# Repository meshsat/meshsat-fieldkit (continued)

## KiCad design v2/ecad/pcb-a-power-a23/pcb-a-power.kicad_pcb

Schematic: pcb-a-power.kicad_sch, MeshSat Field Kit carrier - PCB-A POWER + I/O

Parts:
C1, C2: 47u 25V; C_1206_3216Metric
C3, C29, C30, C35, C36, C41, C42, C47, C48, C54, C120: 10u 25V 1210; C_1210_3225Metric
C4, C19: 1u; C_0603_1608Metric
C5, C26, C53, C57, C68, C75, C86, C98, C100, C102: 10n; C_0603_1608Metric
C6, C58, C69, C76, C87: 100p; C_0603_1608Metric
C7, C59, C70, C77, C88: 47n; C_0603_1608Metric
C8, C60, C71, C78, C89: 4.7u; C_0805_2012Metric
C9, C10, C16, C17, C61, C62, C72, C73, C79, C80, C90, C91: 100n 25V; C_0603_1608Metric
C11, C12, C13, C14, C15, C63, C64, C65, C66, C67, C74, C81, C82, C92, C108, C109, C110, C111, C116, C117, C118, C119: 10u 50V X7R 1210; C_1210_3225Metric
C18: 3.3u; C_0805_2012Metric
C20, C21, C22: 10u 35V 1210; C_1210_3225Metric
C23, C24, C25: 22u 25V 1210; C_1210_3225Metric
C27: 1n; C_0603_1608Metric
C28, C34, C40, C46, C52, C93, C95, C99, C101, C103, C104, C106, C107: 100n; C_0603_1608Metric
C31, C32, C33, C37, C38, C39, C43, C44, C45, C49, C50, C51, C55, C56: 22u 10V X7R 1210; C_1210_3225Metric
C83, C84, C85: 10u 100V X7R 1210; C_1210_3225Metric
C94: 220n; C_0603_1608Metric
C96, C97: 330p; C_0603_1608Metric
C112, C113, C114, C115: 3.3n; C_0603_1608Metric
D1: SMCJ18A (VBAT clamp); D_SMC; LCSC C374030
D2: SMCJ33A (VIN_RAW clamp behind E6's filter); D_SMC
D3: SMBJ5.0A; D_SMB
D4: SMBJ18A (VBUS clamp at the outlet); D_SMB
F1: 25 A mini blade (Keystone 3568 holder): pack node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; Fuseholder_Blade_Mini_Keystone_3568
J_5V_DEV: USB device rail to B16 (JST-VH): + -; JST_VH_B2P-VH_1x02_P3.96mm_Vertical; LCSC C274411
J_5V_S1: slot 1 5.1 V rail to B16 (JST-VH, 16 AWG): + -; JST_VH_B2P-VH_1x02_P3.96mm_Vertical; LCSC C274411
J_5V_S2: slot 2 5.1 V rail to B16 (JST-VH, 16 AWG): + -; JST_VH_B2P-VH_1x02_P3.96mm_Vertical; LCSC C274411
J_5V_S3: slot 3 5.1 V rail to B16 (JST-VH, 16 AWG): + -; JST_VH_B2P-VH_1x02_P3.96mm_Vertical; LCSC C274411
J_54V: 54 V to the PoE injector on B16 (JST-VH): + -; JST_VH_B2P-VH_1x02_P3.96mm_Vertical; LCSC C274411
J_AB1: A-B interconnect (IDC 2x13, top side) to B16's un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; IDC-Header_2x13_P2.54mm_Vertical_NarrowPad
J_AB2: A-B wall-port ribbon (IDC 2x5): the wall USB pair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; IDC-Header_2x05_P2.54mm_Vertical_NarrowPad
J_BM1, J_BM2, J_BM3, J_BM4, J_BM5, J_BM6, J_BM7, J_BM8, J_BM9, J_BM10, J_BM11: SMP-MAX slide-on receptacle R222M00720 (underside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; Radiall_SMPMAX_R222M00720
J_CN1, J_CN2, J_CN3, J_CN4: 9 A spring pin, pack return (Mill-Max 0858 class,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; Mill-Max_0858_power_pin
J_CP1, J_CP2, J_CP3, J_CP4: 9 A spring pin, CELL+ (Mill-Max 0858 class, dock 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; Mill-Max_0858_power_pin
J_DOCK: spring pins to the dock block (2x6, Preci-Dip 813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; PogoPins_2x6
J_HEAT: JST-XH 1x2 socket: the heater mat under the 2590 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; JST_XH_B2B-XH-A_1x02_P2.50mm_Vertical; LCSC C265283
J_HF: 12.0 V to the QMX HF unit in its lid tray (JST-VH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; JST_VH_B2P-VH_1x02_P3.96mm_Vertical; LCSC C274411
J_MAINSW: JST-XH 1x2 socket: the MAIN button lead from the 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; JST_XH_B2B-XH-A_1x02_P2.50mm_Vertical; LCSC C265283
J_MEZZ1: D8 mezzanine harness (IDC 2x8): its USB pair, the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; IDC-Header_2x08_P2.54mm_Vertical_NarrowPad
J_MEZZ_PWR1: D8 mezzanine 5 V (JST-VH): + -; JST_VH_B2P-VH_1x02_P3.96mm_Vertical; LCSC C274411
J_MON: monitor supply lead to the Xenarc (JST-VH): + -; JST_VH_B2P-VH_1x02_P3.96mm_Vertical; LCSC C274411
J_PA: 13.8 V to the PA module on the face plate (JST-VH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; JST_VH_B2P-VH_1x02_P3.96mm_Vertical; LCSC C274411
J_PRE1: pre-charge pin, longer, mates first (32.24 AX); Mill-Max_0858_power_pin
J_RF1, J_RF2, J_RF3, J_RF4, J_RF5, J_RF6, J_RF7, J_RF8, J_RF9, J_RF10, J_RF11: SMA jack, Amphenol 132134-11 vertical (pigtail to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; SMA_Amphenol_132134-11_Vertical; LCSC C3174425
J_USBC_OUT: wall USB-C outlet, power side (pigtail header): V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; PinHeader_1x05_P2.54mm_Vertical
J_USBW: JST-PH 1x4 socket: the wall USB-C data pair to B1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; JST_PH_B4B-PH-K_1x04_P2.00mm_Vertical; LCSC C131334
L1: 10uH XAL1010-103ME (Isat 14 A); L_Coilcraft_XAL1010-XXX
L2: 3.3uH XAL6030-332ME (Isat 12.2 A); L_Coilcraft_XAL6060-XXX
L3, L4, L5, L6: 4.7uH XAL6060-472ME (Isat 11 A); L_Coilcraft_XAL6060-XXX
L7: 4.7uH XAL4030-472ME; L_Coilcraft_XAL4030-XXX
L8: 6.8uH XAL1010-682ME (Isat 17 A); L_Coilcraft_XAL1010-XXX
L9, L11: 6.8uH XAL1010-682ME; L_Coilcraft_XAL1010-XXX
L10: 22uH XAL1010-223ME (Isat 9 A); L_Coilcraft_XAL1010-XXX
Q1: 2N7002: panel controller high = pull KILL low = p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; SOT-23
Q2, Q3, Q4, Q5, Q17, Q18, Q19, Q20: CSD19532Q5B 100 V N-FET (4.6 mOhm at VGS 6 V, Pow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; PowerPAK_SO-8_Single; LCSC C473333
Q6: 2N7002: CHG_INHIBIT high = ILIM_HIZ low = charger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; SOT-23
Q7, Q8, Q9, Q10, Q11, Q12, Q13, Q14, Q15, Q16, Q21, Q22, Q23, Q24, Q25, Q26: CSD18510Q5B 40 V N-FET; PowerPAK_SO-8_Single
Q27: CSD18510Q5B 40 V N-FET (VBUS switch); PowerPAK_SO-8_Single
R1: 10R 2W 2512; R_2512_6332Metric
R2, R3, R4, R5, R13, R21, R30, R34, R38, R42, R57, R73, R102, R103, R104, R111, R112, R113, R114, R116, R118, R123, R128, R143, R145: 100k; R_0603_1608Metric
R6: 240k 1%; R_0603_1608Metric
R7, R15, R29, R33, R37, R41, R49, R51, R59, R61, R67, R75, R125, R134: 10k 1%; R_0603_1608Metric
R8, R52, R62, R68, R78: 40.2k (300 kHz); R_0603_1608Metric
R9, R53, R63, R69, R79: 30k (slope); R_0603_1608Metric
R10, R22, R23, R25, R44, R54, R64, R70, R80, R91, R95, R99, R110, R117, R142: 10k; R_0603_1608Metric
R11, R65, R81, R138: 10mOhm 1% 2512 (ISNS); R_2512_6332Metric
R12, R56, R122, R127: 5mOhm 1% 2512 (CS); R_2512_6332Metric
R14, R58, R74, R124, R133: 62k 1%; R_0603_1608Metric
R16: 10mOhm 1% 2512 (RAC, input current sense); R_2512_6332Metric
R17: 5mOhm 1% 2512 (RSR, charge current sense); R_2512_6332Metric
R18: 10R; R_0603_1608Metric
R19: 16.5k 1%; R_0603_1608Metric
R20: 34.8k 1%; R_0603_1608Metric
R24: 10k (PSYS load); R_0603_1608Metric
R26: 60.4k 1% (CELL_BATPRESZ: 4S per Table, from VDDA); R_0603_1608Metric
R27: 40.2k 1%; R_0603_1608Metric
R28, R32, R36, R40: 53.6k 1%; R_0603_1608Metric
R31, R35, R39, R43: 5mOhm 1% 2512 (shunt); R_2512_6332Metric
R45, R46, R47, R115: 68k (RT: 500 kHz); R_0603_1608Metric
R48: 31.6k 1%; R_0603_1608Metric
R50: 162k 1%; R_0603_1608Metric
R55: 2mOhm 1% 2512 (ISNS); R_2512_6332Metric
R60: 140k 1%; R_0603_1608Metric
R66: 665k 1%; R_0603_1608Metric
R71: 20mOhm 1% 2512 (ISNS); R_2512_6332Metric
R72: 10mOhm 1% 2512 (CS); R_2512_6332Metric
R76: 105k 1%; R_0603_1608Metric
R77: 20k 1% (R_FBL); R_0603_1608Metric
R90: 750R 1% (ILM: 1.2 A); R_0603_1608Metric
R92, R96, R100: 100k 1%; R_0603_1608Metric
R93, R97, R101: 10k 1% (OVLO); R_0603_1608Metric
R94: 909R 1% (ILM: 1.0 A); R_0603_1608Metric
R98: 453R 1% (ILM: 2.0 A); R_0603_1608Metric
R119, R120, R121, R126, R135: 100k (MODE: CCM); R_0603_1608Metric
R129, R130, R131, R132: 22k; R_0603_1608Metric
R136: 21.0k 1% (R_FBL2: 9 V when CTL2 is low); R_0603_1608Metric
R137: 14.0k 1% (R_FBL1: 15 V when CTL1 is low too); R_0603_1608Metric
R139: 43R 1W 2512 (DSCG); R_2512_6332Metric
R140: 1M (GD to VPWR, 9.1.3); R_0603_1608Metric
R141: 698k; R_0603_1608Metric
TP3: EXP2_SP3; TestPoint_Pad_D1.5mm
TP4: EXP2_SP4; TestPoint_Pad_D1.5mm
TP5: EXP2_SP5; TestPoint_Pad_D1.5mm
TP6: EXP2_SP6; TestPoint_Pad_D1.5mm
TP7: EXP2_SP7; TestPoint_Pad_D1.5mm
TP8: EXP2_SP8; TestPoint_Pad_D1.5mm
TP9: VBAT; TestPoint_Pad_D1.5mm
TP10: GND; TestPoint_Pad_D1.5mm
TP11: +3V3; TestPoint_Pad_D1.5mm
TP12: VBUS20; TestPoint_Pad_D1.5mm
TP13: VIN_RAW; TestPoint_Pad_D1.5mm
TP14: CELL+; TestPoint_Pad_D1.5mm
TP15: EMCON_HW; TestPoint_Pad_D1.5mm
TP16: RAIL_EN; TestPoint_Pad_D1.5mm
TP17: SDA; TestPoint_Pad_D1.5mm
TP18: SCL; TestPoint_Pad_D1.5mm
TP19: IADPT; TestPoint_Pad_D1.5mm
TP20: IBAT; TestPoint_Pad_D1.5mm
TP21: DOCK_SPARE; TestPoint_Pad_D1.5mm
TP22: REGN; TestPoint_Pad_D1.5mm
TP23: EXP2_SPA; TestPoint_Pad_D1.5mm
TP24: EXP2_SPB; TestPoint_Pad_D1.5mm
TP25: EXP2_SPC; TestPoint_Pad_D1.5mm
TP26: EXP2_SPD; TestPoint_Pad_D1.5mm
TP27: AB_SPARE; TestPoint_Pad_D1.5mm
U1: LTC2954CTS8-1 push-button on/off controller; TSOT-23-8; LCSC C683782
U2: LM5176PWPR buck-boost controller, VBUS20 from VIN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; HTSSOP-28-1EP_4.4x9.7mm_P0.65mm_EP2.85x5.4mm; LCSC C442493
U3: BQ25731RSNR 1 to 5 cell buck-boost charger, 4S fr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; QFN-32-1EP_4x4mm_P0.4mm_EP2.65x2.65mm; LCSC C2871872
U4: AP64500SP-13 5 A buck, 5.1 V rail +5V_S1; SOIC-8-1EP_3.9x4.9mm_P1.27mm_EP2.29x3mm; LCSC C2070920
U5: AP64500SP-13 5 A buck, 5.1 V rail +5V_S2; SOIC-8-1EP_3.9x4.9mm_P1.27mm_EP2.29x3mm; LCSC C2070920
U6: AP64500SP-13 5 A buck, 5.1 V rail +5V_S3; SOIC-8-1EP_3.9x4.9mm_P1.27mm_EP2.29x3mm; LCSC C2070920
U7: AP64500SP-13 5 A buck, 5.1 V rail +5V_DEV; SOIC-8-1EP_3.9x4.9mm_P1.27mm_EP2.29x3mm; LCSC C2070920
U8: INA226 rail monitor +5V_S1; VSSOP-10_3x3mm_P0.5mm; LCSC C49851
U9: INA226 rail monitor +5V_S2; VSSOP-10_3x3mm_P0.5mm; LCSC C49851
U10: INA226 rail monitor +5V_S3; VSSOP-10_3x3mm_P0.5mm; LCSC C49851
U11: INA226 rail monitor +5V_DEV; VSSOP-10_3x3mm_P0.5mm; LCSC C49851
U12: TPS62933DRLR 3 A buck, 3.3 V logic; SOT-583-8; LCSC C3200405
U13: LM5176PWPR buck-boost controller, +13V8_PA from V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; HTSSOP-28-1EP_4.4x9.7mm_P0.65mm_EP2.85x5.4mm; LCSC C442493
U14: INA226 PA rail monitor (0x46); VSSOP-10_3x3mm_P0.5mm; LCSC C49851
U15: LM5176PWPR buck-boost controller, +12V_HF from VB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; HTSSOP-28-1EP_4.4x9.7mm_P0.65mm_EP2.85x5.4mm; LCSC C442493
U16: LM5176PWPR buck-boost controller, +54V_POE from V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; HTSSOP-28-1EP_4.4x9.7mm_P0.65mm_EP2.85x5.4mm; LCSC C442493
U17: INA226 PoE rail monitor (0x47); VSSOP-10_3x3mm_P0.5mm; LCSC C49851
U18: TPS25740ARGER USB-C PD source controller, 45 W ou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; QFN-24-1EP_4x4mm_P0.5mm_EP2.5x2.5mm; LCSC C544309
U19: LM5176PWPR buck-boost controller, PD_VPWR from VB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; HTSSOP-28-1EP_4.4x9.7mm_P0.65mm_EP2.85x5.4mm; LCSC C442493
U21: TPS259631DDAR eFuse VBAT -> VMON (750R 1% (ILM: 1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; SOIC-8-1EP_3.9x4.9mm_P1.27mm_EP2.29x3mm; LCSC C2155778
U22: TPS259631DDAR eFuse VBAT -> VHEAT (909R 1% (ILM: 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; SOIC-8-1EP_3.9x4.9mm_P1.27mm_EP2.29x3mm; LCSC C2155778
U23: TPS259631DDAR eFuse +5V_DEV -> +5V_D8 (453R 1% (I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; SOIC-8-1EP_3.9x4.9mm_P1.27mm_EP2.29x3mm; LCSC C2155778
U26: SN74LVC08APWR quad AND: EMCON gates for the PA ra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; TSSOP-14_4.4x5mm_P0.65mm; LCSC C465737
U27: PCA9555PW (0x21): enables and status; TSSOP-24_4.4x7.8mm_P0.65mm; LCSC C2864778
U28: PCA9555PW (0x24): power-good lines, spares; TSSOP-24_4.4x7.8mm_P0.65mm; LCSC C2864778
U29: USBLC6-2SC6; SOT-23-6; LCSC C7519

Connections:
+3V3: C55.1, C56.1, C104.1, C106.1, C107.1, D3.1 (A1), J_MEZZ1.13, L7.2, R3.2, R13.2, R22.2, R23.2, R44.2, R48.1, R57.2, R73.2, R91.2, R95.2, R99.2, R110.2, R117.2, R123.2, R128.2, R142.2, TP11.1, U8.6, U9.2, U9.6, U10.1, U10.6, U11.1, U11.2, U11.6, U14.1, U14.6, U17.1, U17.6, U26.14, U27.21 (A0), U27.24 (VDD), U28.3 (A2), U28.24 (VDD)
/+5V_D8: J_MEZZ_PWR1.1, U23.5
/+5V_DEV: C49.1, C50.1, C51.1, C103.1, J_5V_DEV.1, R40.1, R43.2, R100.1, U11.8, U11.9, U18.17, U23.4, U29.5 (VBUS)
/+5V_S1: C31.1, C32.1, C33.1, J_5V_S1.1, R28.1, R31.2, U8.8, U8.9
/+5V_S2: C37.1, C38.1, C39.1, J_5V_S2.1, R32.1, R35.2, U9.8, U9.9
/+5V_S3: C43.1, C44.1, C45.1, J_5V_S3.1, R36.1, R39.2, U10.8, U10.9
/+12V_HF: C109.1, C110.1, C111.1, J_HF.1, R60.1, R65.2, U15.12, U15.13, U15.24
/+13V8_PA: C65.1, C66.1, C67.1, J_PA.1, R50.1, R55.2, U13.12, U13.13, U13.24, U14.8, U14.9
/+54V_POE: C83.1, C84.1, C85.1, J_54V.1, R66.1, R71.2, U16.12, U16.13, U17.9
/AB_SPARE: J_MEZZ1.16, TP27.1
/B33_BST: C52.1, U12.6
/B33_FB: R48.2, R49.1, U12.8
/B33_SS: C53.1, U12.7
/B33_SW: C52.2, L7.1, U12.5
/CELL+: F1.1, J_CP1.1, J_CP2.1, J_CP3.1, J_CP4.1, R1.2, R17.2, TP14.1, U3.19
/CHG_ILIM: Q6.3 (D), R19.2, R20.1, U3.6
/CHG_INHIBIT: Q6.1 (G), R21.1, U27.4 (IO0_0)
/CHRG_OK: R22.1, U3.4, U27.13 (IO1_0)
/CH_ACN: C20.1, C21.1, C22.1, Q7.5, R16.2, U3.2
/CH_BTST1: C16.1, U3.30
/CH_BTST2: C17.1, U3.25
/CH_CELL: R26.2, R27.1, U3.18
/CH_COMP1: R25.1, U3.16
/CH_COMP1C: C26.1, R25.2
/CH_COMP2: C27.1, U3.17
/CH_HIDRV1: Q7.4, U3.31
/CH_HIDRV2: Q10.4, U3.24
/CH_LODRV1: Q8.4, U3.29
/CH_LODRV2: Q9.4, U3.26
/CH_SRP: C23.1, C24.1, C25.1, Q10.5, R17.1, U3.20, U3.22
/CH_SW1: C16.2, L2.1, Q7.1, Q7.2, Q7.3, Q8.5, U3.32
/CH_SW2: C17.2, L2.2, Q9.5, Q10.1, Q10.2, Q10.3, U3.23
/CH_VDDA: C19.1, R18.2, R26.1, U3.7
/D8_EN: R113.1, U23.3, U27.7 (IO0_3)
/D8_FLT: R99.1, U23.6, U27.17 (IO1_4)
/DEV_EN: R42.1, U7.3, U27.11 (IO0_7)
/DOCK_SPARE: J_DOCK.12, TP21.1, U27.18 (IO1_5)
/EMCON_HW: J_AB1.15, R102.1, TP15.1, U26.1, U26.4
/EXP2_SP3: TP3.1, U28.15 (IO1_2)
/EXP2_SP4: TP4.1, U28.16 (IO1_3)
/EXP2_SP5: TP5.1, U28.17 (IO1_4)
/EXP2_SP6: TP6.1, U28.18 (IO1_5)
/EXP2_SP7: TP7.1, U28.19 (IO1_6)
/EXP2_SP8: TP8.1, U28.20 (IO1_7)
/EXP2_SPA: TP23.1, U28.4 (IO0_0)
/EXP2_SPB: TP24.1, U28.5 (IO0_1)
/EXP2_SPC: TP25.1, U28.6 (IO0_2)
/EXP2_SPD: TP26.1, U28.7 (IO0_3)
/EXP_INT: J_AB1.13, J_MEZZ1.12, R110.1, U27.1 (~INT), U28.1 (~INT)
/FE_BOOT1: C9.1, U2.26
/FE_BOOT2: C10.1, U2.20
/FE_COMP: C6.1, R10.1, U2.9
/FE_COMPC: C5.1, R10.2
/FE_CS: Q3.1, Q3.2, Q3.3, Q4.1, Q4.2, Q4.3, R12.1, U2.16
/FE_EN: R14.2, R15.1, U2.1
/FE_FB: R6.2, R7.1, U2.11
/FE_HDRV1: Q2.4, U2.27
/FE_HDRV2: Q5.4, U2.19
/FE_LDRV1: Q3.4, U2.25
/FE_LDRV2: Q4.4, U2.21
/FE_MODE: R119.1, U2.4
/FE_OUT: Q5.5, R11.1, U2.14
/FE_PGOOD: R13.1, U2.17, U27.20 (IO1_7)
/FE_RT: R8.1, U2.6
/FE_SLOPE: R9.1, U2.7
/FE_SS: C7.1, U2.8
/FE_SW1: C9.2, L1.1, Q2.1, Q2.2, Q2.3, Q3.5, U2.28
/FE_SW2: C10.2, L1.2, Q4.5, Q5.1, Q5.2, Q5.3, U2.18
/FE_VCC: C8.1, R119.2, U2.23
/HEAT_EN: R112.1, U22.3, U27.6 (IO0_2)
/HEAT_FLT: R95.1, U22.6, U27.16 (IO1_3)
/HF_BOOT1: C72.1, U15.26
/HF_BOOT2: C73.1, U15.20
/HF_COMP: C69.1, R64.1, U15.9
/HF_COMPC: C68.1, R64.2
/HF_CS: Q16.1, Q16.2, Q16.3, Q23.1, Q23.2, Q23.3, R122.1, U15.16
/HF_EN: R124.1, R124.2, R125.1, U15.1, U26.6
/HF_FB: R60.2, R61.1, U15.11
/HF_HDRV1: Q15.4, U15.27
/HF_HDRV2: Q24.4, U15.19
/HF_LDRV1: Q16.4, U15.25
/HF_LDRV2: Q23.4, U15.21
/HF_MODE: R126.1, U15.4
/HF_OUT: Q24.5, R65.1, U15.14
/HF_PGOOD: R123.1, U15.17, U28.10 (IO0_6)
/HF_RT: R62.1, U15.6
/HF_SLOPE: R63.1, U15.7
/HF_SS: C70.1, U15.8
/HF_SW1: C72.2, L9.1, Q15.1, Q15.2, Q15.3, Q16.5, U15.28
/HF_SW2: C73.2, L9.2, Q23.5, Q24.1, Q24.2, Q24.3, U15.18
/HF_SW_EN: R104.1, U26.5, U27.10 (IO0_6)
/HF_VCC: C71.1, R126.2, U15.23
/IADPT: TP19.1, U3.8
/IBAT: TP20.1, U3.9
/INA_ALERT: R44.1, U8.3, U9.3, U10.3, U11.3, U14.3, U17.3, U27.19 (IO1_6)
/KILL: Q1.3 (D), R4.1, U1.8
/MAIN_PB: J_MAINSW.1, U1.2
/MON_EN: R111.1, U21.3, U27.5 (IO0_1)
/MON_FLT: R91.1, U21.6, U27.15 (IO1_2)
/PA_BOOT1: C61.1, U13.26
/PA_BOOT2: C62.1, U13.20
/PA_COMP: C58.1, R54.1, U13.9
/PA_COMPC: C57.1, R54.2
/PA_CS: Q12.1, Q12.2, Q12.3, Q13.1, Q13.2, Q13.3, R56.1, U13.16
/PA_EN: J_MEZZ1.9, R58.1, R58.2, R59.1, U13.1, U26.3
/PA_FB: R50.2, R51.1, U13.11
/PA_HDRV1: Q11.4, U13.27
/PA_HDRV2: Q14.4, U13.19
/PA_LDRV1: Q12.4, U13.25
/PA_LDRV2: Q13.4, U13.21
/PA_MODE: R120.1, U13.4
/PA_OUT: Q14.5, R55.1, U13.14, U14.10
/PA_PGOOD: R57.1, U13.17, U28.8 (IO0_4)
/PA_RT: R52.1, U13.6
/PA_SLOPE: R53.1, U13.7
/PA_SS: C59.1, U13.8
/PA_SW1: C61.2, L8.1, Q11.1, Q11.2, Q11.3, Q12.5, U13.28
/PA_SW2: C62.2, L8.2, Q13.5, Q14.1, Q14.2, Q14.3, U13.18
/PA_SW_EN: R103.1, U26.2, U27.9 (IO0_5)
/PA_VCC: C60.1, R120.2, U13.23
/PD_BOOT1: C90.1, U19.26
/PD_BOOT2: C91.1, U19.20
/PD_CC1: C96.1, J_USBC_OUT.2, U18.2
/PD_CC2: C97.1, J_USBC_OUT.3, U18.3
/PD_COMP: C87.1, R80.1, U19.9
/PD_COMPC: C86.1, R80.2
/PD_CS: Q22.1, Q22.2, Q22.3, Q25.1, Q25.2, Q25.3, R127.1, U19.16
/PD_CTL1: R137.2, U18.6
/PD_CTL2: R136.2, U18.7
/PD_DSCG: R139.1, U18.24
/PD_DVDD: C94.1, U18.5, U18.8, U18.12, U18.13
/PD_EN: R133.1, R133.2, R134.1, R143.1, U19.1, U28.13 (IO1_0)
/PD_FB: R76.2, R77.1, R136.1, R137.1, U19.11
/PD_GD: R140.2, R141.1, U18.15
/PD_GDNG: Q27.4, U18.22
/PD_HDRV1: Q21.4, U19.27
/PD_HDRV2: Q26.4, U19.19
/PD_LDRV1: Q22.4, U19.25
/PD_LDRV2: Q25.4, U19.21
/PD_MODE: R135.1, U19.4
/PD_OUT: Q26.5, R81.1, U19.14
/PD_PGOOD: R128.1, U19.17, U28.11 (IO0_7)
/PD_RT: R78.1, U19.6
/PD_SLOPE: R79.1, U19.7
/PD_SS: C88.1, U19.8
/PD_SW: Q27.1, Q27.2, Q27.3, R138.1, U18.19, U18.23
/PD_SW1: C90.2, L11.1, Q21.1, Q21.2, Q21.3, Q22.5, U19.28
/PD_SW2: C91.2, L11.2, Q25.5, Q26.1, Q26.2, Q26.3, U19.18
/PD_UFP: R142.1, U18.11, U28.14 (IO1_1)
/PD_VAUX: C95.1, U18.14, U18.16
/PD_VBUS: C120.1, D4.1 (A1), J_USBC_OUT.1, R138.2, R139.2, U18.21
/PD_VCC: C89.1, R135.2, U19.23
/PD_VPWR: C117.1, C118.1, C119.1, Q27.5, R76.1, R81.2, R140.1, U18.20, U19.12, U19.13, U19.24
/PD_VTX: C93.1, U18.1
/PI_KILL: J_AB1.10, Q1.1 (G), R5.1
/PI_SHDN_REQ: J_AB1.9, R3.1, U1.5
/POE_BOOT1: C79.1, U16.26
/POE_BOOT2: C80.1, U16.20
/POE_COMP: C76.1, R70.1, U16.9
/POE_COMPC: C75.1, R70.2
/POE_CS: Q18.1, Q18.2, Q18.3, Q19.1, Q19.2, Q19.3, R72.1, U16.16
/POE_EN: R74.1, R74.2, R75.1, R114.1, U16.1, U27.8 (IO0_4)
/POE_FB: R66.2, R67.1, U16.11
/POE_HDRV1: Q17.4, U16.27
/POE_HDRV2: Q20.4, U16.19
/POE_LDRV1: Q18.4, U16.25
/POE_LDRV2: Q19.4, U16.21
/POE_MODE: R121.1, U16.4
/POE_OUT: Q20.5, R71.1, U16.14, U17.10
/POE_PGOOD: R73.1, U16.17, U28.9 (IO0_5)
/POE_RT: R68.1, U16.6
/POE_SLOPE: R69.1, U16.7
/POE_SS: C77.1, U16.8
/POE_SW1: C79.2, L10.1, Q17.1, Q17.2, Q17.3, Q18.5, U16.28
/POE_SW2: C80.2, L10.2, Q19.5, Q20.1, Q20.2, Q20.3, U16.18
/POE_VCC: C78.1, R121.2, U16.23
/PRECHG: J_PRE1.1, R1.1
/PROCHOT: R23.1, U3.11, U27.14 (IO1_1)
/PSYS: R24.1, U3.10
/RAIL_EN: R2.1, TP16.1, U1.6, U12.2
/REGN: C18.1, R18.1, R19.1, TP22.1, U3.28
/RF_5G1: J_BM8.1 (In), J_RF8.1 (In)
/RF_5G2: J_BM9.1 (In), J_RF9.1 (In)
/RF_GNSS: J_BM4.1 (In), J_RF4.1 (In)
/RF_HF: J_BM2.1 (In), J_RF2.1 (In)
/RF_IRIDIUM: J_BM10.1 (In), J_RF10.1 (In)
/RF_LORA: J_BM11.1 (In), J_RF11.1 (In)
/RF_P2PA: J_BM6.1 (In), J_RF6.1 (In)
/RF_P2PB: J_BM7.1 (In), J_RF7.1 (In)
/RF_SDR: J_BM5.1 (In), J_RF5.1 (In)
/RF_VHF: J_BM1.1 (In), J_RF1.1 (In)
/RF_WIFI24: J_BM3.1 (In), J_RF3.1 (In)
/S1_BOOT: C28.1, U4.1
/S1_COMP: R129.1, U4.6
/S1_COMPC: C112.1, R129.2
/S1_FB: R28.2, R29.1, U4.5
/S1_OUT: L3.2, R31.1, U8.10
/S1_RT: R45.1, U4.4
/S1_SW: C28.2, L3.1, U4.8
/S2_BOOT: C34.1, U5.1
/S2_COMP: R130.1, U5.6
/S2_COMPC: C113.1, R130.2
/S2_FB: R32.2, R33.1, U5.5
/S2_OUT: L4.2, R35.1, U9.10
/S2_RT: R46.1, U5.4
/S2_SW: C34.2, L4.1, U5.8
/S3_BOOT: C40.1, U6.1
/S3_COMP: R131.1, U6.6
/S3_COMPC: C114.1, R131.2
/S3_FB: R36.2, R37.1, U6.5
/S3_OUT: L5.2, R39.1, U10.10
/S3_RT: R47.1, U6.4
/S3_SW: C40.2, L5.1, U6.8
/SCL: J_AB1.12, J_MEZZ1.11, TP18.1, U3.13, U8.5, U9.5, U10.5, U11.5, U14.5, U17.2, U17.5, U27.22 (SCL), U28.22 (SCL)
/SDA: J_AB1.11, J_MEZZ1.10, TP17.1, U3.12, U8.4, U9.4, U10.4, U11.4, U14.2, U14.4, U17.4, U27.23 (SDA), U28.23 (SDA)
/SD_BOOT: C46.1, U7.1
/SD_COMP: R132.1, U7.6
/SD_COMPC: C115.1, R132.2
/SD_FB: R40.2, R41.1, U7.5
/SD_OUT: L6.2, R43.1, U11.10
/SD_RT: R115.1, U7.4
/SD_SW: C46.2, L6.1, U7.8
/SHORE_INHIBIT: J_AB1.21, J_DOCK.8, R118.1
/SLOT_EN1: J_AB1.17, R30.1, U4.3
/SLOT_EN2: J_AB1.18, R34.1, U5.3
/SLOT_EN3: J_AB1.19, R38.1, U6.3
/TR_APRS: J_AB1.14, J_MEZZ1.7, R116.1
/TX_INHIBIT_n: J_AB1.16, J_MEZZ1.8, R145.1
/U21_DVDT: C98.1, U21.2
/U21_ILM: R90.1, U21.7
/U21_OVLO: R92.2, R93.1, U21.8
/U22_DVDT: C100.1, U22.2
/U22_ILM: R94.1, U22.7
/U22_OVLO: R96.2, R97.1, U22.8
/U23_DVDT: C102.1, U23.2
/U23_ILM: R98.1, U23.7
/U23_OVLO: R100.2, R101.1, U23.8
/USB_D8_N: J_AB1.2, J_MEZZ1.2
/USB_D8_P: J_AB1.1, J_MEZZ1.1
/USB_E6_N: J_AB1.26, J_DOCK.10
/USB_E6_P: J_AB1.25, J_DOCK.9
/USB_WALL_N: J_AB2.2, J_USBW.2, U29.3 (I/O2), U29.4 (I/O2)
/USB_WALL_P: J_AB2.1, J_USBW.1, U29.1 (I/O1), U29.6 (I/O1)
/VBAT: C1.1, C2.1, C3.1, C4.1, C29.1, C30.1, C35.1, C36.1, C41.1, C42.1, C47.1, C48.1, C54.1, C63.1, C64.1, C74.1, C81.1, C82.1, C92.1, C99.1, C101.1, C108.1, C116.1, D1.1 (A1), F1.2, Q11.5, Q15.5, Q17.5, Q21.5, R2.2, R4.2, R92.1, R96.1, TP9.1, U1.1, U4.2, U5.2, U6.2, U7.2, U12.3, U13.2, U13.3, U15.2, U15.3, U16.2, U16.3, U16.24, U19.2, U19.3, U21.4, U22.4
/VBUS20: C13.1, C14.1, C15.1, R6.1, R11.2, R16.1, TP12.1, U2.12, U2.13, U2.24, U3.1, U3.3
/VHEAT: J_HEAT.1, U22.5
/VIN_RAW: C11.1, C12.1, D2.1 (A1), J_DOCK.1, J_DOCK.2, J_DOCK.3, J_DOCK.4, Q2.5, R14.1, TP13.1, U2.2, U2.3
/VMON: J_MON.1, U21.5
/ZEROIZE_HW: J_AB1.20, J_MEZZ1.15, R117.1
GND: C1.2, C2.2, C3.2, C4.2, C5.2, C6.2, C7.2, C8.2, C11.2, C12.2, C13.2, C14.2, C15.2, C18.2, C19.2, C20.2, C21.2, C22.2, C23.2, C24.2, C25.2, C26.2, C27.2, C29.2, C30.2, C31.2, C32.2, C33.2, C35.2, C36.2, C37.2, C38.2, C39.2, C41.2, C42.2, C43.2, C44.2, C45.2, C47.2, C48.2, C49.2, C50.2, C51.2, C53.2, C54.2, C55.2, C56.2, C57.2, C58.2, C59.2, C60.2, C63.2, C64.2, C65.2, C66.2, C67.2, C68.2, C69.2, C70.2, C71.2, C74.2, C75.2, C76.2, C77.2, C78.2, C81.2, C82.2, C83.2, C84.2, C85.2, C86.2, C87.2, C88.2, C89.2, C92.2, C93.2, C94.2, C95.2, C96.2, C97.2, C98.2, C99.2, C100.2, C101.2, C102.2, C103.2, C104.2, C106.2, C107.2, C108.2, C109.2, C110.2, C111.2, C112.2, C113.2, C114.2, C115.2, C116.2, C117.2, C118.2, C119.2, C120.2, D1.2 (A2), D2.2 (A2), D3.2 (A2), D4.2 (A2), J_5V_DEV.2, J_5V_S1.2, J_5V_S2.2, J_5V_S3.2, J_54V.2, J_AB1.3, J_AB1.4, J_AB1.5, J_AB1.6, J_AB1.7, J_AB1.8, J_AB1.22, J_AB1.23, J_AB1.24, J_AB2.3, J_AB2.4, J_AB2.5, J_AB2.6, J_AB2.7, J_AB2.8, J_AB2.9, J_AB2.10, J_BM1.2 (Ext), J_BM2.2 (Ext), J_BM3.2 (Ext), J_BM4.2 (Ext), J_BM5.2 (Ext), J_BM6.2 (Ext), J_BM7.2 (Ext), J_BM8.2 (Ext), J_BM9.2 (Ext), J_BM10.2 (Ext), J_BM11.2 (Ext), J_CN1.1, J_CN2.1, J_CN3.1, J_CN4.1, J_DOCK.5, J_DOCK.6, J_DOCK.7, J_DOCK.11, J_HEAT.2, J_HF.2, J_MAINSW.2, J_MEZZ1.3, J_MEZZ1.4, J_MEZZ1.5, J_MEZZ1.6, J_MEZZ1.14, J_MEZZ_PWR1.2, J_MON.2, J_PA.2, J_RF1.2 (Ext), J_RF2.2 (Ext), J_RF3.2 (Ext), J_RF4.2 (Ext), J_RF5.2 (Ext), J_RF6.2 (Ext), J_RF7.2 (Ext), J_RF8.2 (Ext), J_RF9.2 (Ext), J_RF10.2 (Ext), J_RF11.2 (Ext), J_USBC_OUT.4, J_USBC_OUT.5, J_USBW.3, J_USBW.4, Q1.2 (S), Q6.2 (S), Q8.1, Q8.2, Q8.3, Q9.1, Q9.2, Q9.3, R5.2, R7.2, R8.2, R9.2, R12.2, R15.2, R20.2, R21.2, R24.2, R27.2, R29.2, R30.2, R33.2, R34.2, R37.2, R38.2, R41.2, R42.2, R45.2, R46.2, R47.2, R49.2, R51.2, R52.2, R53.2, R56.2, R59.2, R61.2, R62.2, R63.2, R67.2, R68.2, R69.2, R72.2, R75.2, R77.2, R78.2, R79.2, R90.2, R93.2, R94.2, R97.2, R98.2, R101.2, R102.2, R103.2, R104.2, R111.2, R112.2, R113.2, R114.2, R115.2, R116.2, R118.2, R122.2, R125.2, R127.2, R134.2, R141.2, R143.2, R145.2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

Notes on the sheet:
PACK NODE OVER THE DOCK BLOCK (32.56): 9 A PINS, PRE-CHARGE, 25 A BLADE, DOCK SIGNAL PINS
MAIN POWER CONTROL LTC2954
FRONT END: LM5176 FROM THE 9 TO 36 V INPUT TO THE 20 V CHARGE BUS
CHARGER BQ25731: 4S FROM THE 20 V BUS INTO THE PACK NODE, I2C 0x6B
SLOT RAIL S1: AP64500 5.1 V + INA226 0x40
SLOT RAIL S2: AP64500 5.1 V + INA226 0x41
SLOT RAIL S3: AP64500 5.1 V + INA226 0x44
DEVICE RAIL: AP64500 5.1 V + INA226 0x45
3.3 V LOGIC: TPS62933
PA RAIL: LM5176 13.8 V 6 A, EMCON GATED, INA226 0x46
HF RAIL: LM5176 12.0 V 2 A, EMCON GATED
POE RAIL: LM5176 BOOST 54 V 0.6 A, INA226 0x47
USB-C PD OUTLET: TPS25740A + LM5176 5/9/15 V STAGE
EFUSES: MONITOR, HEATER, D8 5 V
EMCON GATES 74LVC08, EXPANDERS 0x21 0x24
RIBBON J_AB1 2x13, MEZZANINE HARNESS J_MEZZ1 2x8, WALL USB DATA
ELEVEN BLIND-MATE RF SITES: SMA JACK (TOP) + SMP-MAX RECEPTACLE (UNDERSIDE)
TEST POINTS, FLAGS
OTHER PARTS (not in a section list)

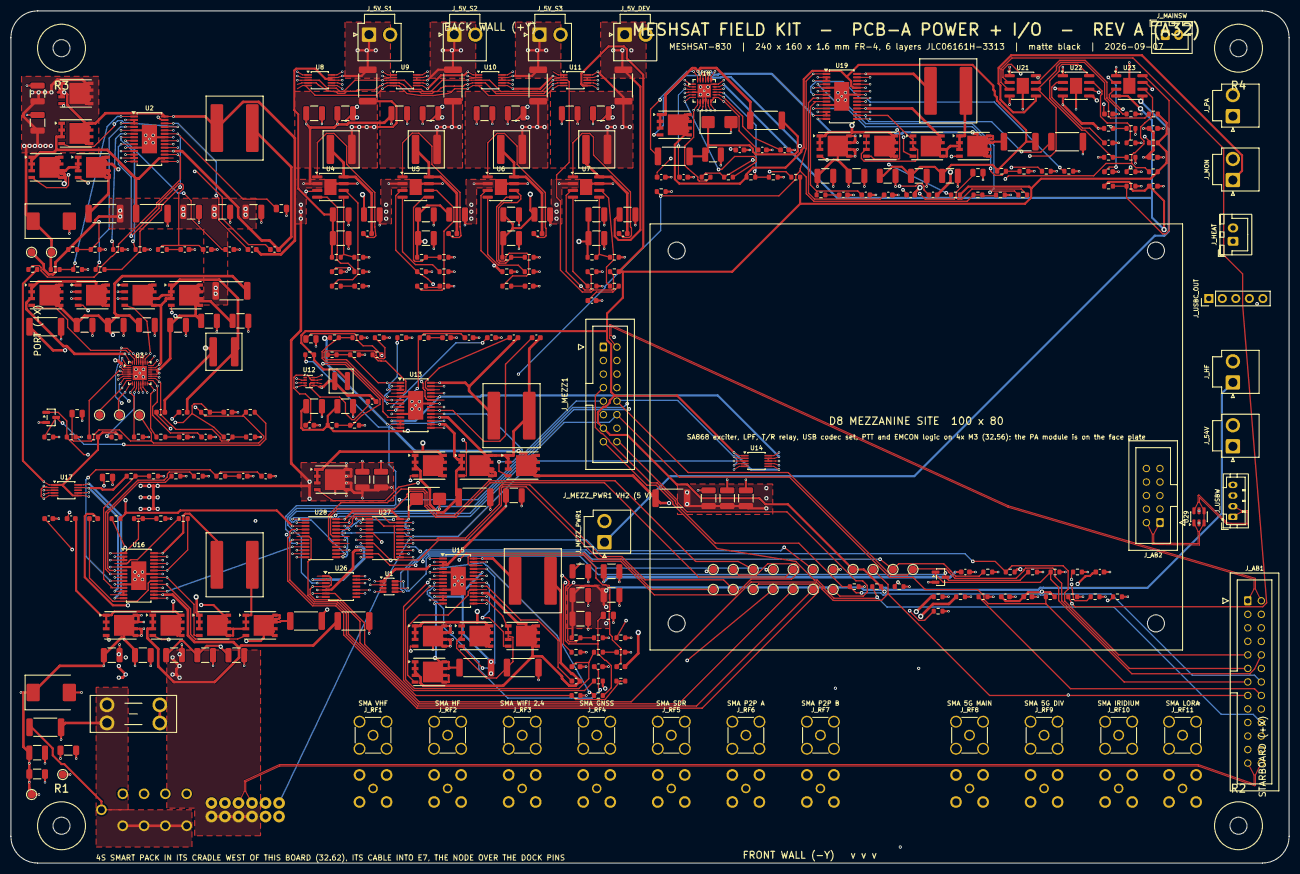
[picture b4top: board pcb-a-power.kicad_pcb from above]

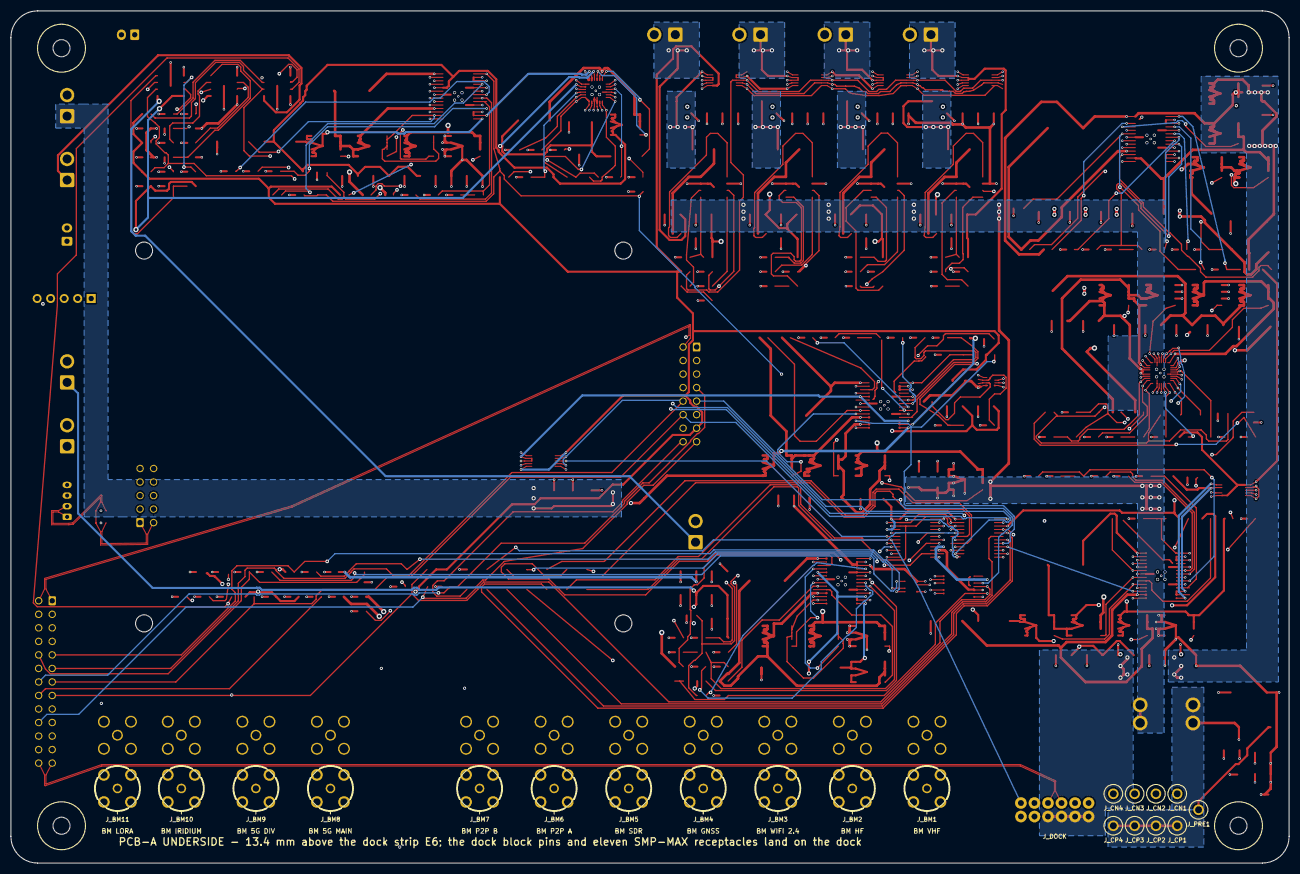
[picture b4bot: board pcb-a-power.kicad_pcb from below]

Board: 6 copper layers, 240.0 x 160.0 mm, 400 parts (21 on the bottom side), 250 nets.

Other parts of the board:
H1: M3 rod R1; MountingHole_3.2mm_M3
H2: M3 rod R2; MountingHole_3.2mm_M3
H3: M3 rod R3; MountingHole_3.2mm_M3
H4: M3 rod R4; MountingHole_3.2mm_M3
H5, H6, H7, H8: M3 standoff, mezzanine; MountingHole_3.2mm_M3

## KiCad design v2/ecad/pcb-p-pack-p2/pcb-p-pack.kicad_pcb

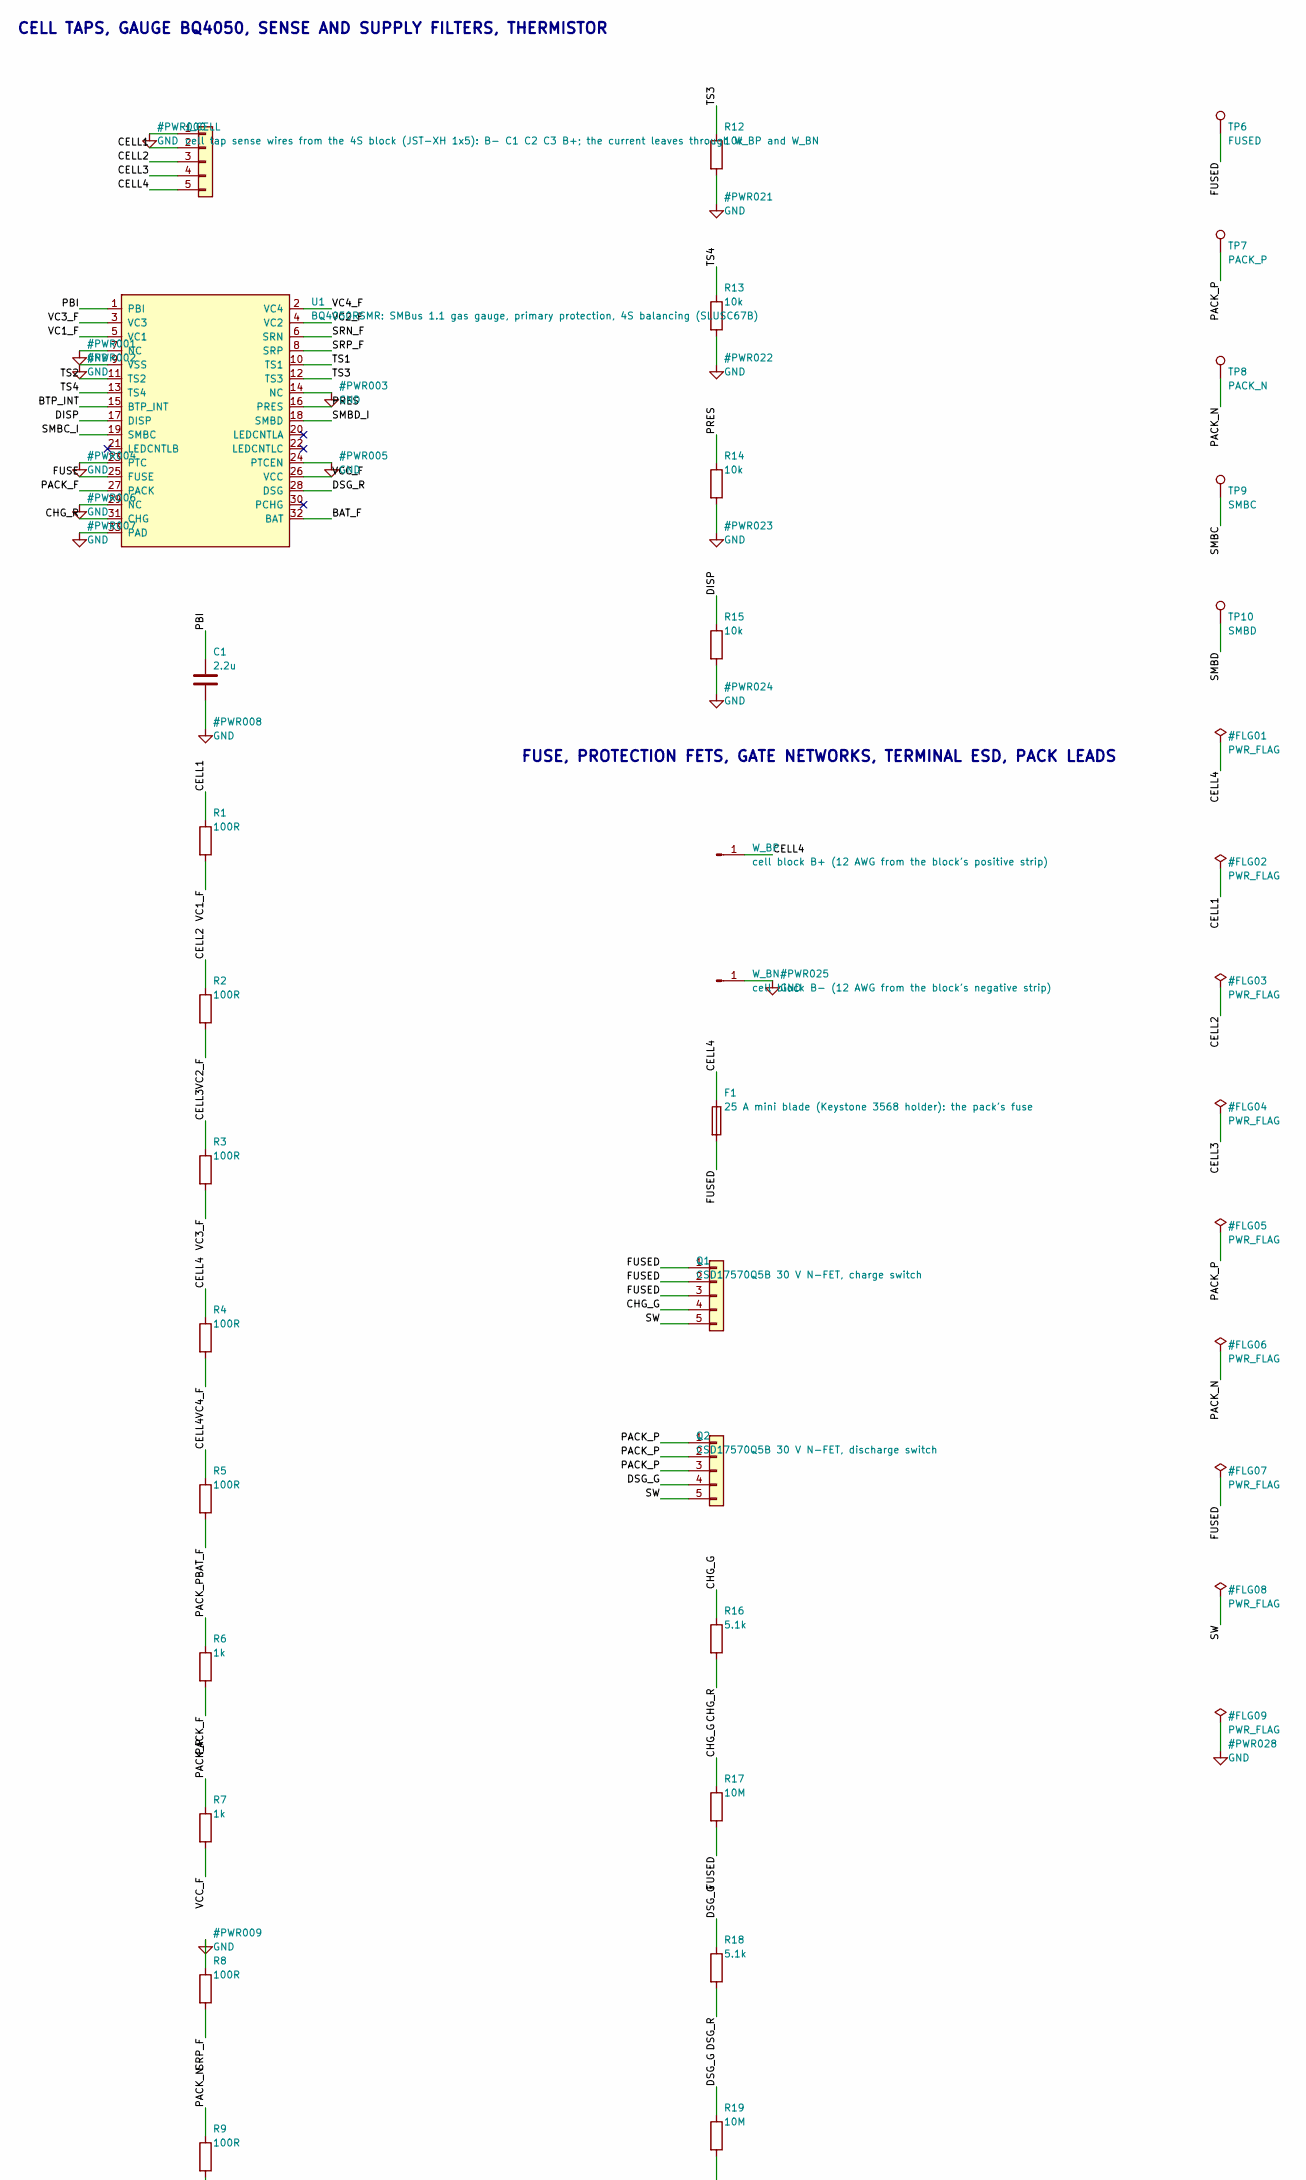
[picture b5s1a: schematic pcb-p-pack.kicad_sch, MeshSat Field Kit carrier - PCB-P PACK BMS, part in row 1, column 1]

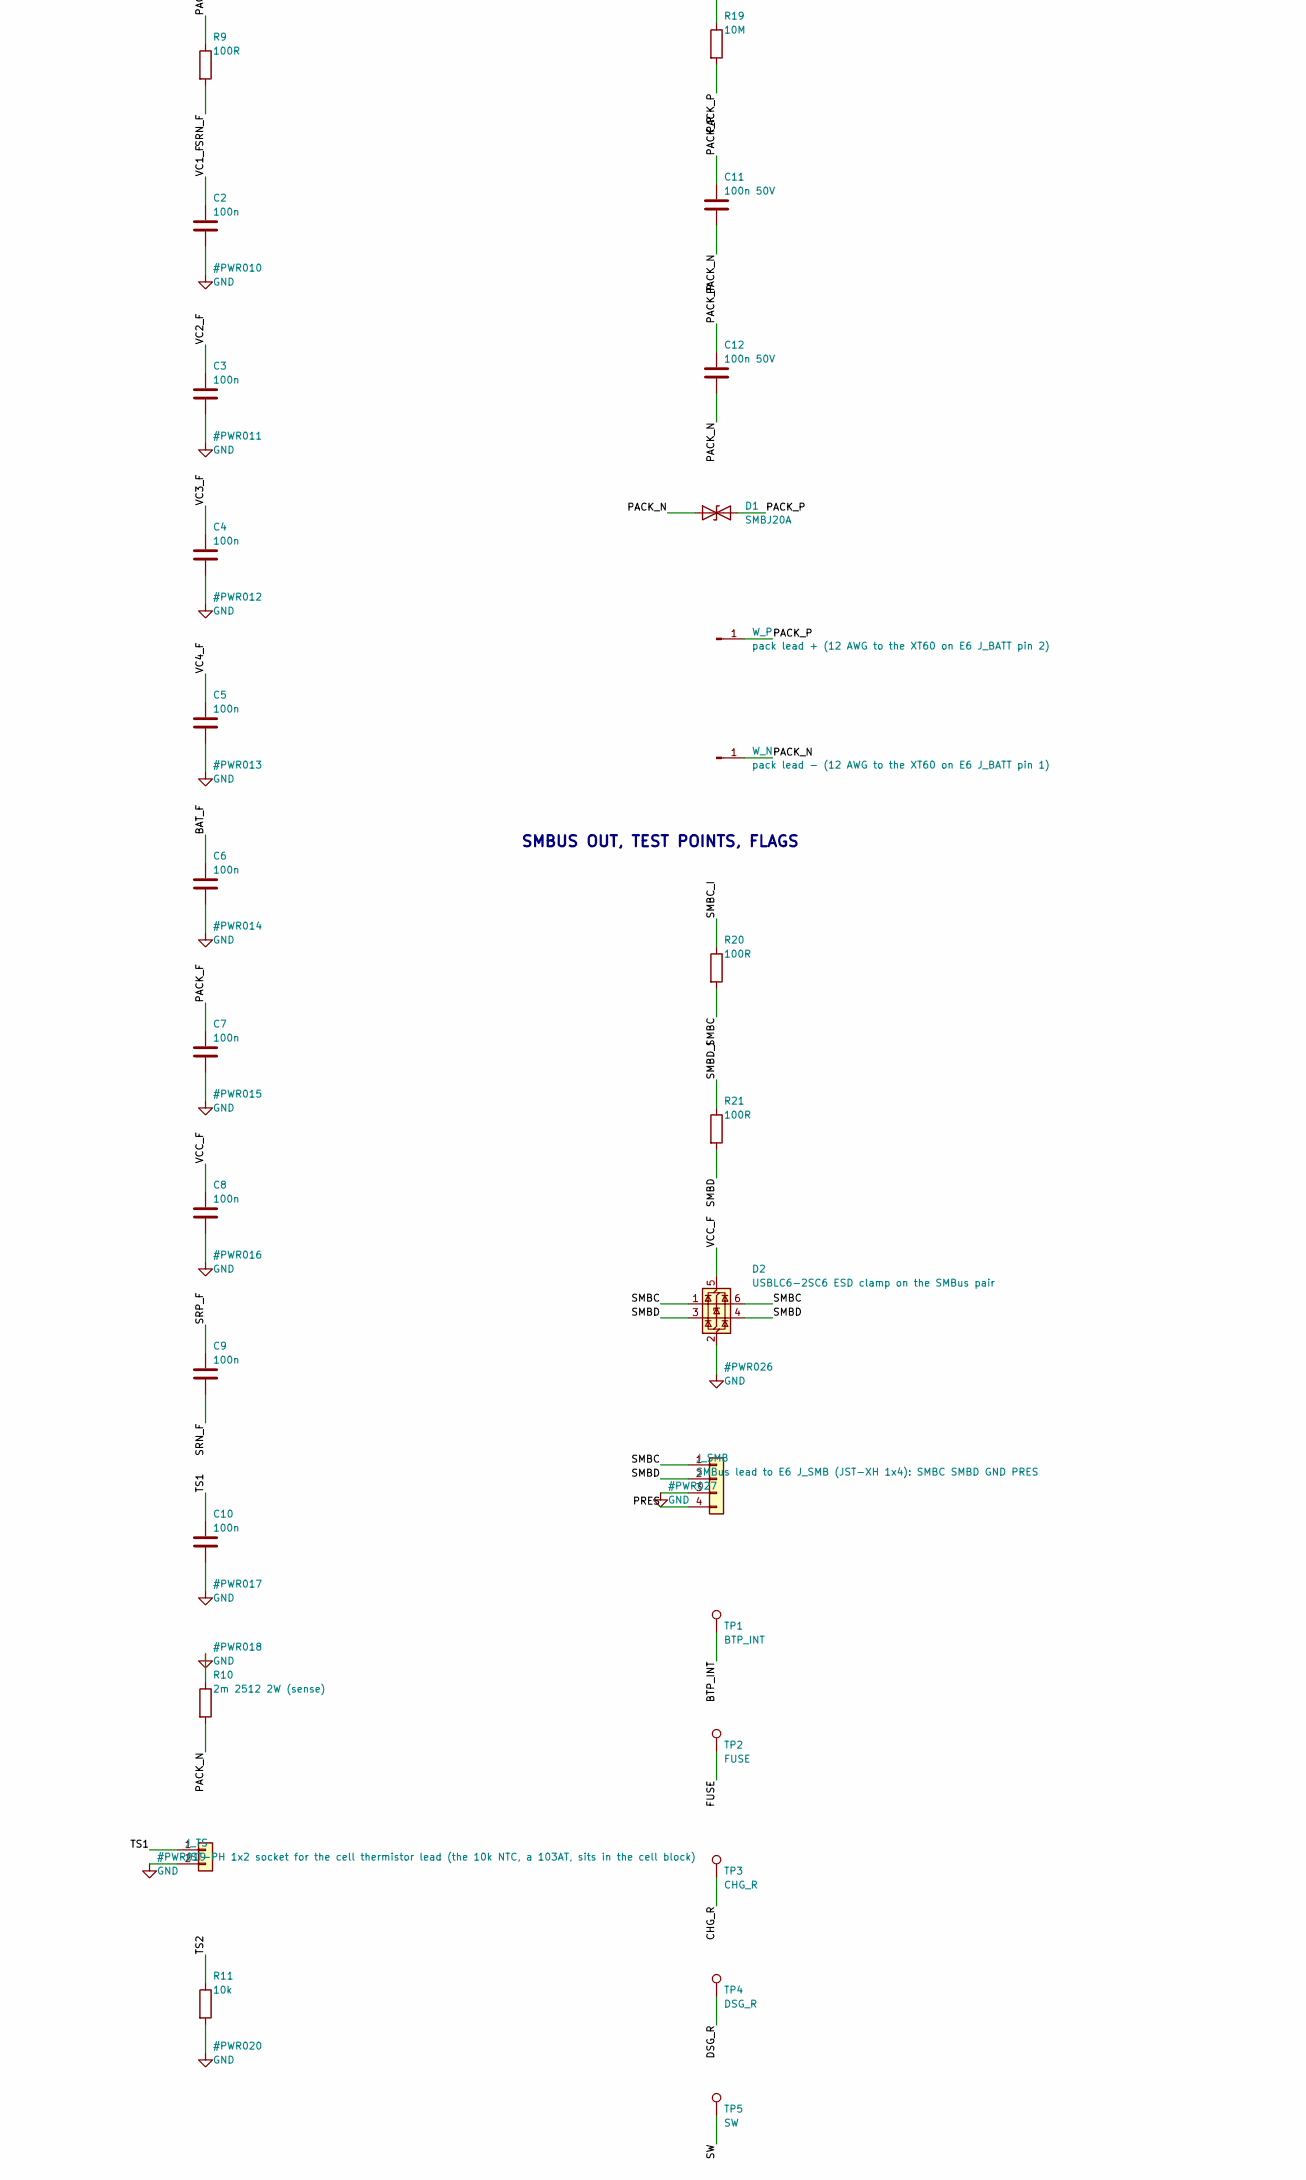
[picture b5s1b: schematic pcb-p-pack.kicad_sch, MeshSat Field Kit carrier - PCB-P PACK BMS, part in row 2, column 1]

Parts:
C1: 2.2u; C_0805_2012Metric
C2, C3, C4, C5, C6, C7, C8, C9, C10: 100n; C_0603_1608Metric
C11: 100n 50V; C_0603_1608Metric
C12: 100n 50V; C_1206_3216Metric
D1: SMBJ20A; D_SMB
D2: USBLC6-2SC6 ESD clamp on the SMBus pair; SOT-23-6; LCSC C7519
F1: 25 A mini blade (Keystone 3568 holder): the pack'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; Fuseholder_Blade_Mini_Keystone_3568
J_CELL: cell tap sense wires from the 4S block (JST-XH 1x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; JST_XH_B5B-XH-A_1x05_P2.50mm_Vertical
J_SMB: SMBus lead to E6 J_SMB (JST-XH 1x4): SMBC SMBD GN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; JST_XH_B4B-XH-A_1x04_P2.50mm_Vertical
J_TS: JST-PH 1x2 socket for the cell thermistor lead (t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; JST_PH_B2B-PH-K_1x02_P2.00mm_Vertical; LCSC C5251182
Q1: CSD17570Q5B 30 V N-FET, charge switch; PowerPAK_SO-8_Single; LCSC C529279
Q2: CSD17570Q5B 30 V N-FET, discharge switch; PowerPAK_SO-8_Single; LCSC C529279
R1, R2, R3, R4, R5, R8, R9, R20, R21: 100R; R_0603_1608Metric
R6, R7: 1k; R_0603_1608Metric
R10: 2m 2512 2W (sense); R_2512_6332Metric
R11, R12, R13, R14, R15: 10k; R_0603_1608Metric
R16, R18: 5.1k; R_0603_1608Metric
R17, R19: 10M; R_0603_1608Metric
TP1: BTP_INT; TestPoint_Pad_D1.5mm
TP2: FUSE; TestPoint_Pad_D1.5mm
TP3: CHG_R; TestPoint_Pad_D1.5mm
TP4: DSG_R; TestPoint_Pad_D1.5mm
TP5: SW; TestPoint_Pad_D1.5mm
TP6: FUSED; TestPoint_Pad_D1.5mm
TP7: PACK_P; TestPoint_Pad_D1.5mm
TP8: PACK_N; TestPoint_Pad_D1.5mm
TP9: SMBC; TestPoint_Pad_D1.5mm
TP10: SMBD; TestPoint_Pad_D1.5mm
U1: BQ4050RSMR: SMBus 1.1 gas gauge, primary protecti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; QFN-32-1EP_5x5mm_P0.5mm_EP3.1x3.1mm; LCSC C157570
W_BN: cell block B- (12 AWG from the block's negative s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; SolderWire-2.5sqmm_1x01_D2.4mm_OD3.6mm
W_BP: cell block B+ (12 AWG from the block's positive s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; SolderWire-2.5sqmm_1x01_D2.4mm_OD3.6mm
W_N: pack lead - (12 AWG to the XT60 on E6 J_BATT pin 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; SolderWire-2.5sqmm_1x01_D2.4mm_OD3.6mm
W_P: pack lead + (12 AWG to the XT60 on E6 J_BATT pin 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; SolderWire-2.5sqmm_1x01_D2.4mm_OD3.6mm

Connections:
/BAT_F: C6.1, R5.2, U1.32 (BAT)
/BTP_INT: TP1.1, U1.15 (BTP_INT)
/CELL1: J_CELL.2, R1.1
/CELL2: J_CELL.3, R2.1
/CELL3: J_CELL.4, R3.1
/CELL4: F1.1, J_CELL.5, R4.1, R5.1, W_BP.1
/CHG_G: Q1.4, R16.1, R17.1
/CHG_R: R16.2, TP3.1, U1.31 (CHG)
/DISP: R15.1, U1.17 (DISP)
/DSG_G: Q2.4, R18.1, R19.1
/DSG_R: R18.2, TP4.1, U1.28 (DSG)
/FUSE: TP2.1, U1.25 (FUSE)
/FUSED: F1.2, Q1.1, Q1.2, Q1.3, R17.2, TP6.1
/PACK_F: C7.1, R6.2, U1.27 (PACK)
/PACK_N: C11.2, C12.2, D1.1 (A1), R9.1, R10.2, TP8.1, W_N.1
/PACK_P: C11.1, C12.1, D1.2 (A2), Q2.1, Q2.2, Q2.3, R6.1, R7.1, R19.2, TP7.1, W_P.1
/PBI: C1.1, U1.1 (PBI)
/PRES: J_SMB.4, R14.1, U1.16 (PRES)
/SMBC: D2.1 (I/O1), D2.6 (I/O1), J_SMB.1, R20.2, TP9.1
/SMBC_I: R20.1, U1.19 (SMBC)
/SMBD: D2.3 (I/O2), D2.4 (I/O2), J_SMB.2, R21.2, TP10.1
/SMBD_I: R21.1, U1.18 (SMBD)
/SRN_F: C9.2, R9.2, U1.6 (SRN)
/SRP_F: C9.1, R8.2, U1.8 (SRP)
/SW: Q1.5, Q2.5, TP5.1
/TS1: C10.1, J_TS.1, U1.10 (TS1)
/TS2: R11.1, U1.11 (TS2)
/TS3: R12.1, U1.12 (TS3)
/TS4: R13.1, U1.13 (TS4)
/VC1_F: C2.1, R1.2, U1.5 (VC1)
/VC2_F: C3.1, R2.2, U1.4 (VC2)
/VC3_F: C4.1, R3.2, U1.3 (VC3)
/VC4_F: C5.1, R4.2, U1.2 (VC4)
/VCC_F: C8.1, D2.5 (VBUS), R7.2, U1.26 (VCC)
GND: C1.2, C2.2, C3.2, C4.2, C5.2, C6.2, C7.2, C8.2, C10.2, D2.2 (GND), J_CELL.1, J_SMB.3, J_TS.2, R8.1, R10.1, R11.2, R12.2, R13.2, R14.2, R15.2, U1.7 (NC), U1.9 (VSS), U1.14 (NC), U1.23 (PTC), U1.24 (PTCEN), U1.29 (NC), U1.33 (PAD), W_BN.1

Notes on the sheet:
CELL TAPS, GAUGE BQ4050, SENSE AND SUPPLY FILTERS, THERMISTOR
FUSE, PROTECTION FETS, GATE NETWORKS, TERMINAL ESD, PACK LEADS
SMBUS OUT, TEST POINTS, FLAGS
